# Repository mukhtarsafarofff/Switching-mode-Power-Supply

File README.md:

- 📐 [Schaltplan (PDF)](hardware/schematic/schematic.pdf)
- 🧭 [PCB-Layout (PDF)](hardware/pcb/layout.pdf)
- 🧾 [Stückliste (BOM)](docs/BOM.xlsx)
- ⚙️ [Firmware Build & Flash](firmware/README.md#build--flash)
- ✅ [Testergebnisse](docs/test-report.md)
## Build & Flash
(ENG)
This schematic shows an AC-to-DC switching mode power supply (SMPS).  
The AC input is first rectified by the bridge rectifier and then smoothed by the bulk capacitor to create a high-voltage DC bus.  
The UC3842 controller generates switching pulses that drive the IRF740 MOSFET.  
The MOSFET rapidly switches the transformer primary, transferring energy in high-frequency pulses instead of using a low-frequency linear conversion method.  
On the secondary side, the output is rectified by a fast diode and filtered by capacitors and an inductor to produce a stable DC voltage.  
A feedback network returns regulation information to the controller so that the output voltage remains controlled under changing load conditions.  
This design improves efficiency, reduces transformer size, and is widely used in compact electronic power supplies.

(DE)

Diese Schaltung zeigt ein AC-zu-DC-Schaltnetzteil (SMPS).  
Die Wechselspannung am Eingang wird zuerst durch den Brückengleichrichter gleichgerichtet und anschließend durch den Siebkondensator zu einer Hochspannungs-Gleichspannung geglättet.  
Der UC3842-Controller erzeugt Schaltimpulse zur Ansteuerung des IRF740-MOSFETs.  
Der MOSFET schaltet die Primärseite des Transformators mit hoher Frequenz, sodass die Energie in Impulsen übertragen wird und keine verlustreiche lineare Wandlung erforderlich ist.  
Auf der Sekundärseite wird die Ausgangsspannung durch eine schnelle Diode gleichgerichtet und durch Spule sowie Kondensatoren geglättet.  
Ein Rückkopplungsnetzwerk liefert Regelinformationen an den Controller zurück, damit die Ausgangsspannung auch bei Laständerungen stabil bleibt.  
Dieses Design bietet einen hohen Wirkungsgrad, kleinere Bauteilgrößen und wird häufig in kompakten Elektroniknetzteilen eingesetzt.
### Build
```bash
pio run

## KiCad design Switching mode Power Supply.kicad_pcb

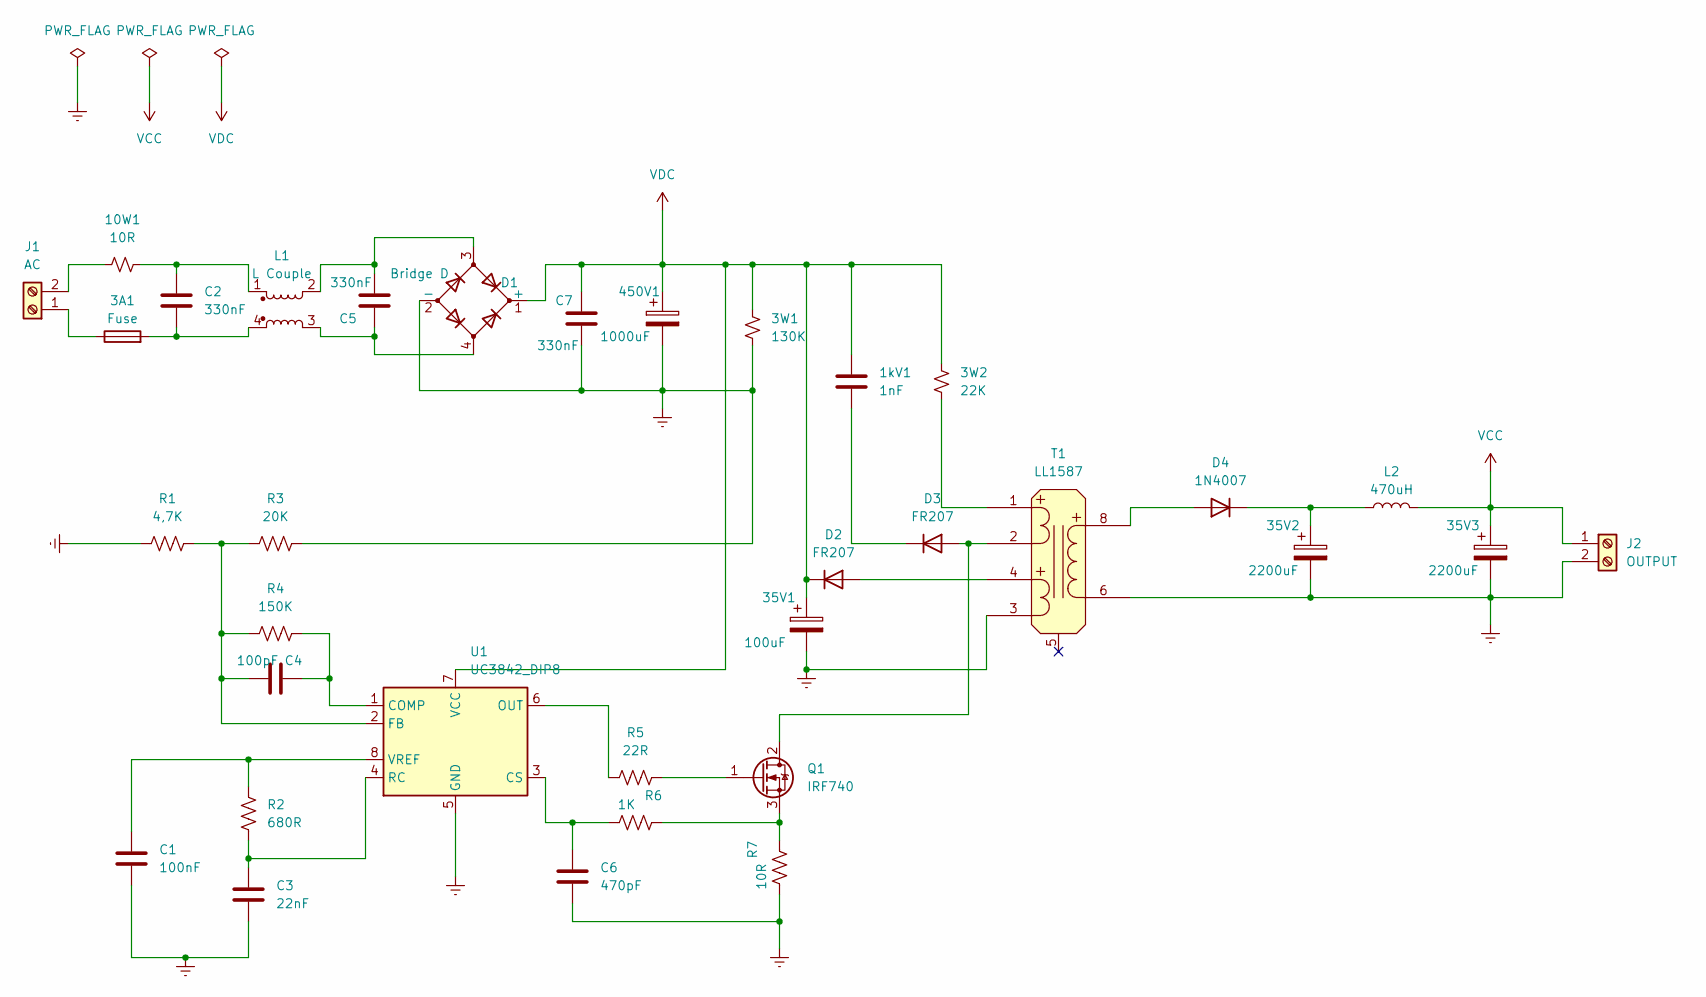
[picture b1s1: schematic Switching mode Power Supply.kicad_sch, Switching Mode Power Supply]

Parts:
1kV1: 1nF; C_Disc_D8.0mm_W5.0mm_P10.00mm
3A1: Fuse; Fuse_Bourns_MF-RHT1000
3W1: 130K; R_Axial_DIN0516_L15.5mm_D5.0mm_P20.32mm_Horizontal
3W2: 22K; R_Axial_DIN0516_L15.5mm_D5.0mm_P20.32mm_Horizontal
10W1: 10R; R_Axial_Power_L25.0mm_W9.0mm_P30.48mm
35V1: 100uF; CP_Radial_D12.5mm_P7.50mm
35V2, 35V3: 2200uF; CP_Radial_D12.5mm_P7.50mm
450V1: 1000uF; CP_Radial_D12.5mm_P7.50mm
C1: 100nF; C_Disc_D8.0mm_W5.0mm_P10.00mm
C2, C5, C7: 330nF; C_Rect_L10.3mm_W5.7mm_P7.50mm_MKS4
C3: 22nF; C_Disc_D8.0mm_W5.0mm_P10.00mm
C4: 100pF; C_Disc_D8.0mm_W5.0mm_P10.00mm
C6: 470pF; C_Disc_D8.0mm_W5.0mm_P10.00mm
D1: Bridge D; Diode_Bridge_Vishay_KBL
D2, D3: FR207; D_DO-41_SOD81_P10.16mm_Horizontal
D4: 1N4007; D_DO-41_SOD81_P10.16mm_Horizontal
J1: AC; TerminalBlock_bornier-2_P5.08mm
J2: OUTPUT; TerminalBlock_bornier-2_P5.08mm
L1: L Couple; L_CommonMode_Wuerth_WE-CMB-S
L2: 470uH; L_Toroid_Vertical_L22.4mm_W10.2mm_P7.90mm_Vishay_TJ4
Q1: IRF740; TO-220-3_Vertical
R1: 4,7K; R_Axial_DIN0309_L9.0mm_D3.2mm_P15.24mm_Horizontal
R2: 680R; R_Axial_DIN0309_L9.0mm_D3.2mm_P15.24mm_Horizontal
R3: 20K; R_Axial_DIN0309_L9.0mm_D3.2mm_P15.24mm_Horizontal
R4: 150K; R_Axial_DIN0309_L9.0mm_D3.2mm_P15.24mm_Horizontal
R5: 22R; R_Axial_DIN0309_L9.0mm_D3.2mm_P15.24mm_Horizontal
R6: 1K; R_Axial_DIN0309_L9.0mm_D3.2mm_P15.24mm_Horizontal
R7: 10R; R_Axial_DIN0309_L9.0mm_D3.2mm_P15.24mm_Horizontal
T1: LL1587; Transformer_Microphone_Lundahl_LL1587
U1: UC3842_DIP8; DIP-8_W7.62mm

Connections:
Earth: 3W1.1, 35V1.2, 35V2.2, 35V3.2, 450V1.2, C1.1, C3.1, C6.1, C7.2, D1.2 (-), J2.2, R1.1, R3.2, R7.1, T1.3 (P2-), T1.6 (S-), U1.5 (GND)
unnamed: 3A1.2, C2.2, L1.4
unnamed: 10W1.2, C2.1, L1.1
unnamed: C5.1, D1.3, L1.2
unnamed: C5.2, D1.4, L1.3
unnamed: D2.2 (A), T1.4 (P2+)
unnamed: D3.2 (A), Q1.2 (D), T1.2 (P1-)
unnamed: 1kV1.1, D3.1 (K)
unnamed: D4.2 (A), T1.8 (S+)
unnamed: 35V2.1, D4.1 (K), L2.1
unnamed: 3A1.1, J1.1
unnamed: 10W1.1, J1.2
unnamed: Q1.1 (G), R5.2
unnamed: Q1.3 (S), R6.2, R7.2
unnamed: 3W2.1, T1.1 (P1+)
unnamed: C4.2, R4.2, U1.1 (COMP)
unnamed: C6.2, R6.1, U1.3 (CS)
unnamed: C4.1, R1.2, R3.1, R4.1, U1.2 (FB)
unnamed: R5.1, U1.6 (OUT)
unnamed: C3.2, R2.2, U1.4 (RC)
unnamed: C1.2, R2.1, U1.8 (VREF)
VCC: 35V3.1, J2.1, L2.2
VDC: 1kV1.2, 3W1.2, 3W2.2, 35V1.1, 450V1.1, C7.1, D1.1 (+), D2.1 (K), U1.7 (VCC)

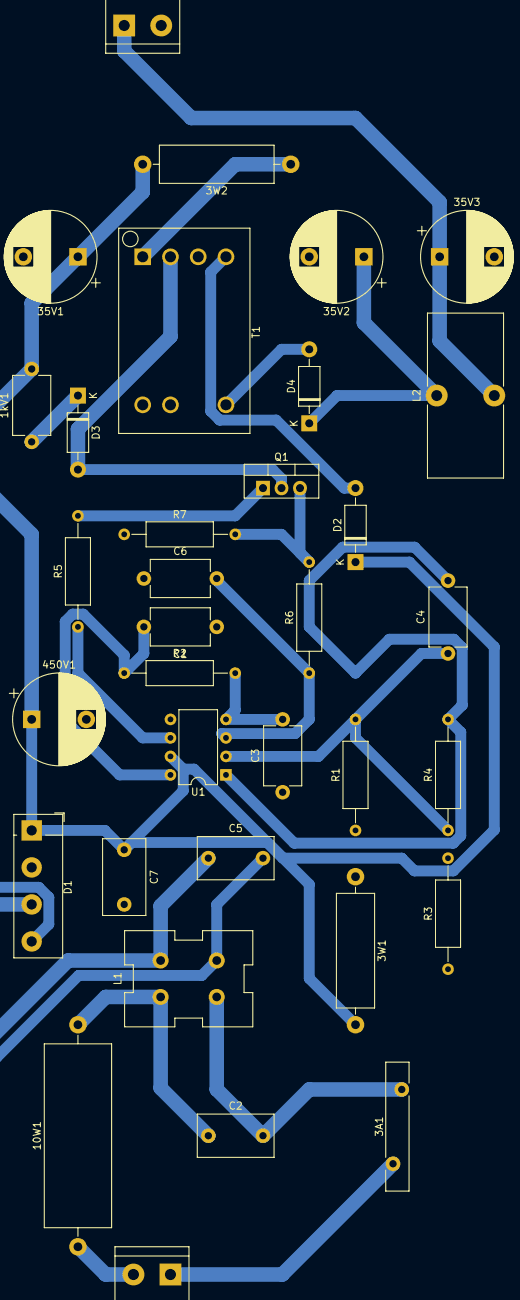
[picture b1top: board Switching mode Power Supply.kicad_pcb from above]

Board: 2 copper layers, 34 parts (0 on the bottom side), 23 nets.

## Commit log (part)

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2024-03-22 Switching Mode Power Supply is accomplished
2024-03-23 Switching mode power supply is restored
2026-04-27 Rename Switching mode Power Supply-B_Cu.pdf to Single-Layer PCB Design
2026-04-27 Rename Switching mode power supply (Drawing).pdf to SMPS Schematic
